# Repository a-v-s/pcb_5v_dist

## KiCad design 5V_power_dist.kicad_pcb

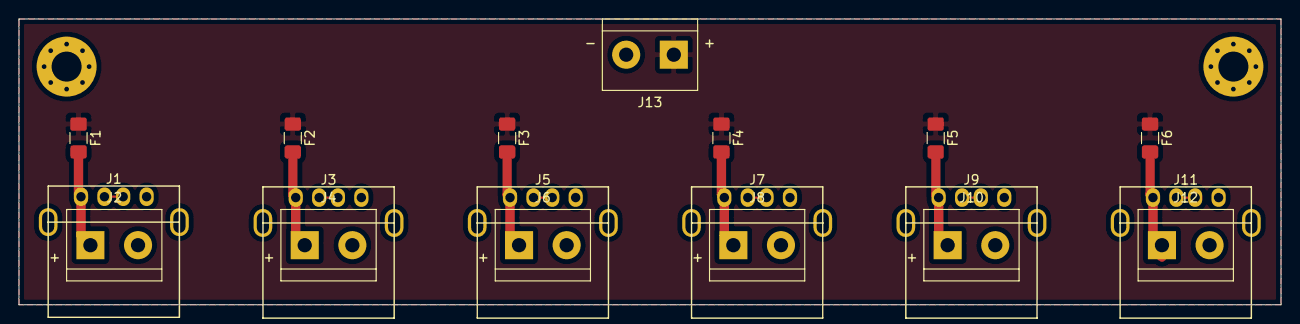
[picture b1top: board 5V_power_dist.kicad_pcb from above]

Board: 2 copper layers, 134.6 x 30.5 mm, 21 parts (0 on the bottom side), 14 nets.

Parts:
F1, F2, F3, F4, F5, F6: Polyfuse; Fuse_1206_3216Metric_Pad1.42x1.75mm_HandSolder
H1, H2: MountingHole; MountingHole_3.2mm_M3_Pad_Via
J1, J3, J5, J7, J9, J11: USB_A; USB_A_Female
J2, J4, J6, J8, J10, J12, J13: Screw_Terminal_01x02; TerminalBlock_bornier-2_P5.08mm

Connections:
+5V: F1.1, F2.1, F3.1, F4.1, F5.1, F6.1, J13.1
GND: J1.4, J1.5, J2.2, J3.4, J3.5, J4.2, J5.4, J5.5, J6.2, J7.4, J7.5, J8.2, J9.4, J9.5, J10.2, J11.4, J11.5, J12.2, J13.2
unnamed: F1.2, J1.1, J2.1
unnamed: F2.2, J3.1, J4.1
unnamed: F3.2, J5.1, J6.1
unnamed: F4.2, J7.1, J8.1
unnamed: F5.2, J9.1, J10.1
unnamed: F6.2, J11.1, J12.1
unnamed: J1.2, J1.3
unnamed: J3.2, J3.3
unnamed: J5.2, J5.3
unnamed: J7.2, J7.3
unnamed: J9.2, J9.3
unnamed: J11.2, J11.3
